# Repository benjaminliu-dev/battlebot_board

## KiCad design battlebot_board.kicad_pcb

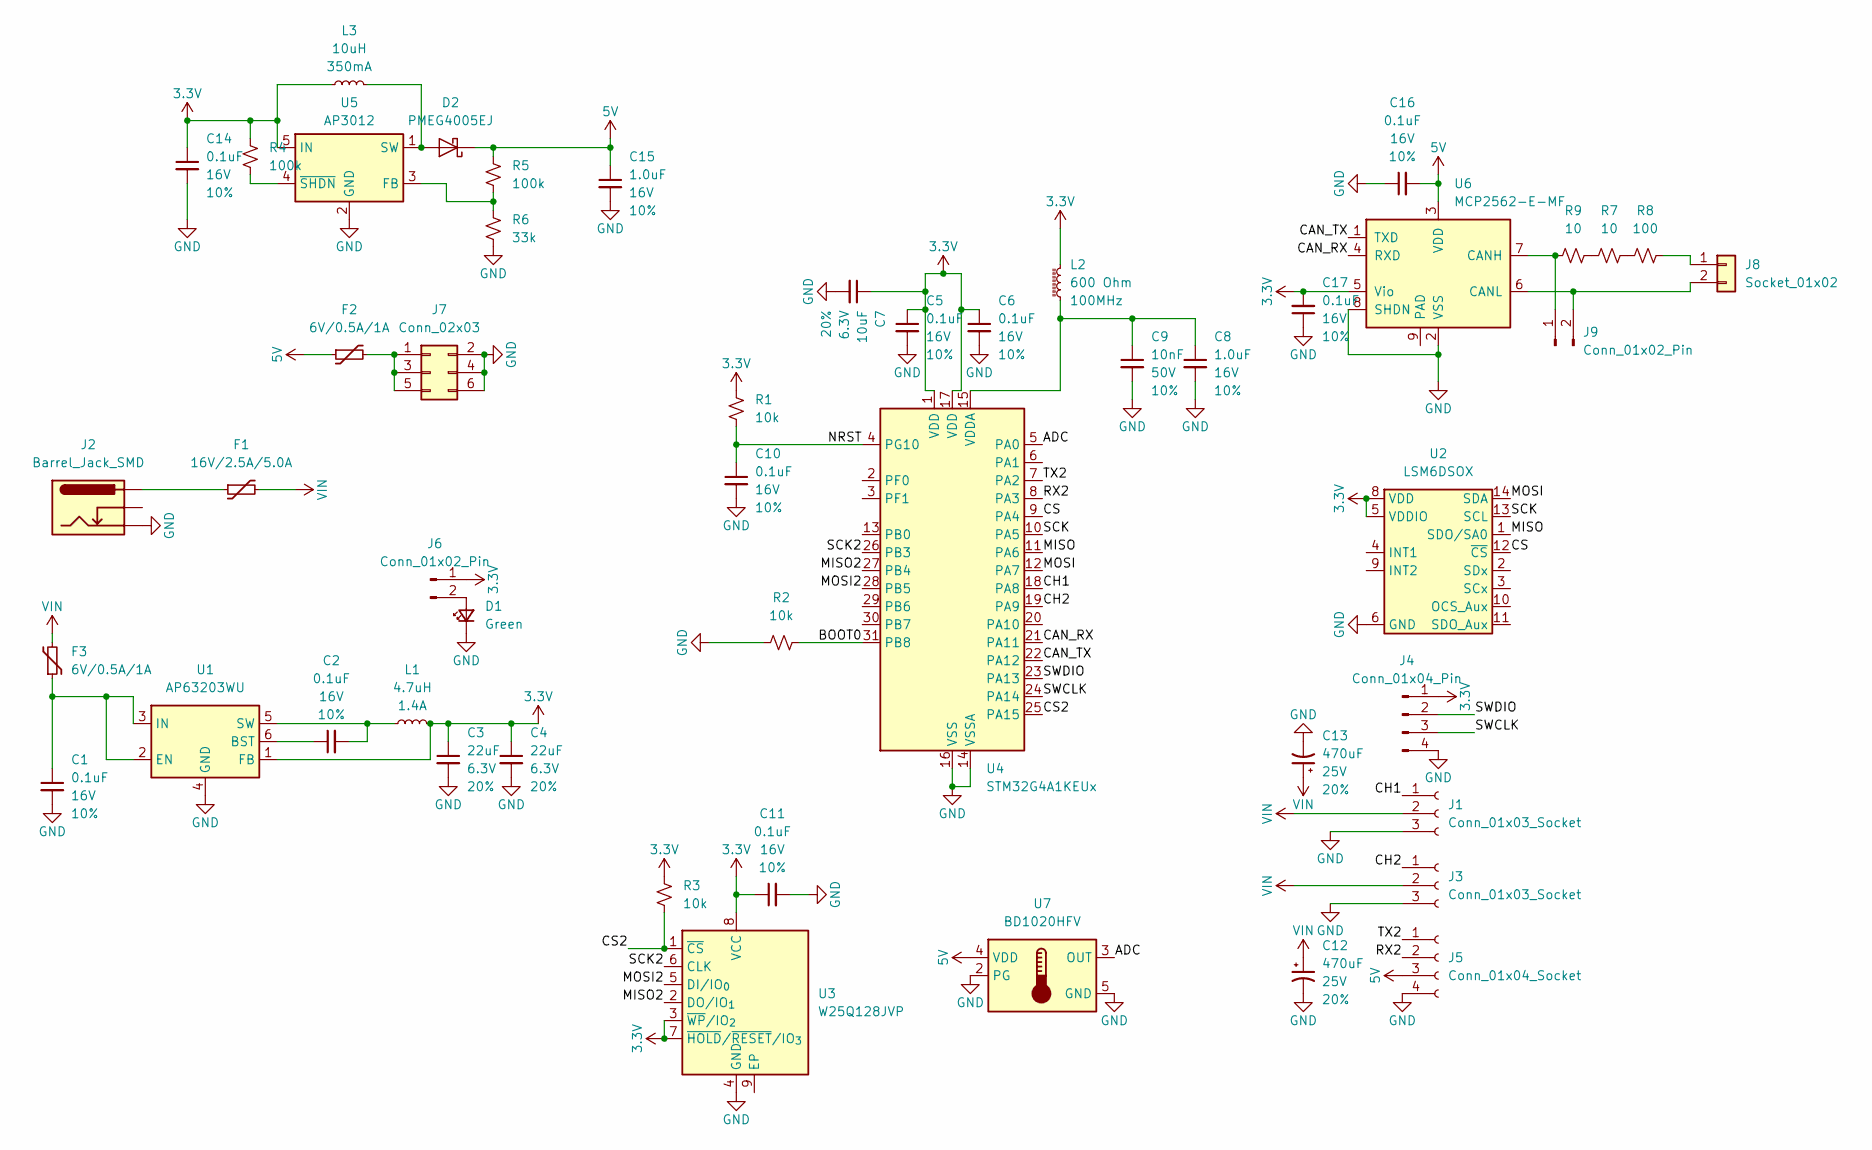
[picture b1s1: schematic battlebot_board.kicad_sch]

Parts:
C1, C2, C5, C6, C10, C11, C14, C16, C17: 0.1uF; C_0402_1005Metric; Voltage 16V; Tolerance 10%
C3, C4: 22uF; C_0603_1608Metric; Voltage 6.3V; Tolerance 20%
C7: 10uF; C_0402_1005Metric; Voltage 6.3V; Tolerance 20%
C8, C15: 1.0uF; C_0402_1005Metric; Voltage 16V; Tolerance 10%
C9: 10nF; C_0402_1005Metric; Voltage 50V; Tolerance 10%
C12, C13: 470uF; Electrolytic_10.3x10.3mm; Voltage 25V; Tolerance 20%
D1: Green; LED_0603_1608Metric_Green
D2: PMEG4005EJ; D_SOD-323F
F1: 16V/2.5A/5.0A; 1812
F2, F3: 6V/0.5A/1A; 0805
J1, J3: Conn_01x03_Socket; JST_1x03_P1.0mm_Vertical_SMD
J2: Barrel_Jack_SMD
J4: Conn_01x04_Pin; PinHeader_1x04_P1.27mm_Vertical
J5: Conn_01x04_Socket; JST_1x04_P1.0mm_Vertical_SMD
J6, J9: Conn_01x02_Pin; PinHeader_1x02_P1.27mm_Vertical
J7: Conn_02x03; PinHeader_2x03_P1.27mm_Vertical; Part Number LL1009-2A, 2.54MM 2*3PIN HEADER,LENGTH=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
J8: Socket_01x02; PinHeader_1x02_P1.27mm_Vertical; Part Number ?
L1: 4.7uH; 1008_2520Metric
L2: 600 Ohm; C_0805_2012Metric
L3: 10uH; C_0805_2012Metric
R1, R2, R3: 10k; R_0402_1005Metric
R4, R5: 100k; R_0402_1005Metric
R6: 33k; R_0402_1005Metric
R7, R9: 10; R_0402_1005Metric
R8: 100; R_0402_1005Metric
U1: AP63203WU; TSOT-23-6
U2: LSM6DSOX; ST_LGA-14L_2.5x3.0mm_P0.5mm_4x3
U3: W25Q128JVP; WSON-8-1EP_6x5mm_P1.27mm_EP3.4x4.3mm
U4: STM32G4A1KEUx; QFN-32-1EP_5x5mm_P0.5mm_EP3.45x3.45mm
U5: AP3012; SOT23-5
U6: MCP2562-E-MF; DFN-8-1EP_3x3mm_P0.65mm_EP1.55x2.4mm
U7: BD1020HFV; HVSOF5

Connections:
3.3V: C3.1, C4.1, C5.1, C6.1, C7.1, C11.1, C14.1, C17.2, J4.1, J6.1, L1.2, L2.2, L3.1, R1.2, R3.2, R4.2, U1.1 (FB), U2.5 (VDDIO), U2.8 (VDD), U3.3 (~WP/IO_{2}), U3.7 (~HOLD/~RESET/IO_{3}), U3.8 (VCC), U4.1 (VDD), U4.17 (VDD), U5.5 (IN), U6.5 (Vio)
5V: C15.1, C16.2, D2.1 (K), F2.1, J5.3, R5.2, U6.3 (VDD), U7.4 (VDD)
/ADC: U4.5 (PA0), U7.3 (OUT)
/BOOT0: R2.2, U4.31 (PB8)
/CAN_RX: U4.21 (PA11), U6.4 (RXD)
/CAN_TX: U4.22 (PA12), U6.1 (TXD)
/CH1: J1.1, U4.18 (PA8)
/CH2: J3.1, U4.19 (PA9)
/CS: U2.12 (~CS), U4.9 (PA4)
/CS2: R3.1, U3.1 (~CS), U4.25 (PA15)
/MISO: U2.1 (SDO/SA0), U4.11 (PA6)
/MISO2: U3.2 (DO/IO_{1}), U4.27 (PB4)
/MOSI: U2.14 (SDA), U4.12 (PA7)
/MOSI2: U3.5 (DI/IO_{0}), U4.28 (PB5)
/NRST: C10.1, R1.1, U4.4 (PG10)
/RX2: J5.2, U4.8 (PA3)
/SCK: U2.13 (SCL), U4.10 (PA5)
/SCK2: U3.6 (CLK), U4.26 (PB3)
/SWCLK: J4.3, U4.24 (PA14)
/SWDIO: J4.2, U4.23 (PA13)
/TX2: J5.1, U4.7 (PA2)
GND: C1.2, C3.2, C4.2, C5.2, C6.2, C7.2, C8.2, C9.2, C10.2, C11.2, C12.2, C13.2, C14.2, C15.2, C16.1, C17.1, D1.1 (K), J1.3, J2.GND, J3.3, J4.4, J5.4, J7.2 (+12V), J7.4 (GND), J7.6 (GND), R2.1, R6.1, U1.4 (GND), U2.6 (GND), U2.7 (GND), U3.4 (GND), U4.14 (VSSA), U4.16 (VSS), U4.32 (VSS), U4.33 (VSS), U5.2 (GND), U6.2 (VSS), U6.8 (SHDN), U7.2 (PG), U7.5 (GND)
unnamed: D1.2 (A), J6.2
unnamed: D2.2 (A), L3.2, U5.1 (SW)
unnamed: F1.1, J2.PWR
unnamed: F2.2, J7.1 (+12V), J7.3 (GND), J7.5 (GND)
unnamed: J8.1, R8.2
unnamed: J8.2, J9.2, U6.6 (CANL)
unnamed: J9.1, R9.1, U6.7 (CANH)
unnamed: R7.1, R9.2
unnamed: R7.2, R8.1
unnamed: C2.1, U1.6 (BST)
unnamed: C1.1, F3.1, U1.2 (EN), U1.3 (IN)
unnamed: C2.2, L1.1, U1.5 (SW)
unnamed: C8.1, C9.1, L2.1, U4.15 (VDDA)
unnamed: R5.1, R6.2, U5.3 (FB)
unnamed: R4.1, U5.4 (~SHDN)
VIN: C12.1, C13.1, F1.2, F3.2, J1.2, J3.2

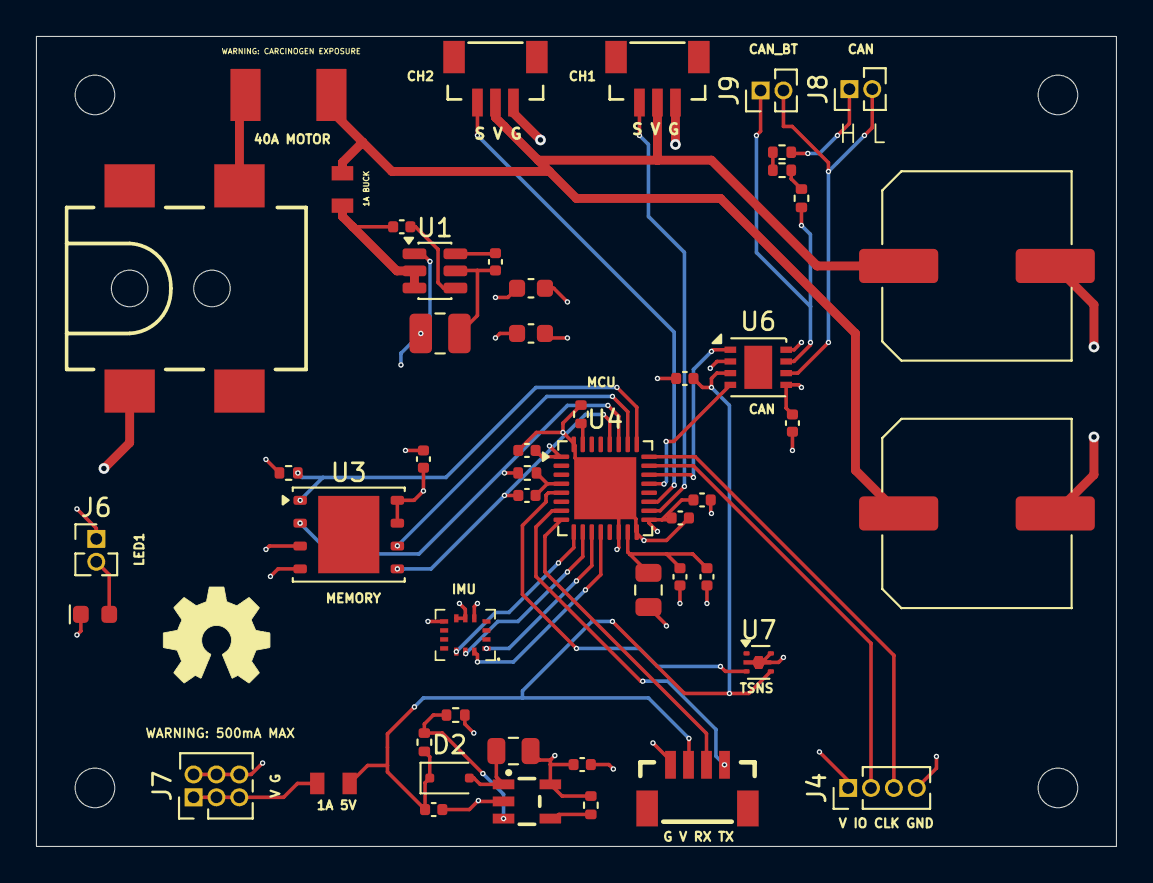
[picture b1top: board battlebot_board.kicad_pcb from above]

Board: 4 copper layers, 60.0 x 45.0 mm, 51 parts (0 on the bottom side), 38 nets.

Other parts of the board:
Ref**: Val**; OSHW_Logo_6mm
